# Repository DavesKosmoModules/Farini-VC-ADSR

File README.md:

# Farini-VC-ADSR

Voltage controlled AD / ADSR

- Envelope generator switchable between ADSR & AD
- Loopable
- End Of Cycle output
- Output can be inverted for ducking

- When in AD mode use the trigger input
- When in ADSR mode, use the gate input to start envelope, the trigger input will retigger the attach phase
- When in cycle mode use no inputs

 Contained are schematics & gerber files for pcb fabrication of both electrical and front panel. This is sutiable for entry level however a basic level of electronics, soldering, fault finding, and some basic tools are required.

 [Schematic](/Docs/Farini-Schematic.pdf)
 
 [BOM](Docs/Farini-BOM.pdf)

 If you wish to edit in ki-cad the following dependencies are required, however the component values will need tidying on the PCB as I use a forked version with no values.
 
  https://github.com/holmesrichards/Kosmo_panel
  
  https://github.com/holmesrichards/aoKicad

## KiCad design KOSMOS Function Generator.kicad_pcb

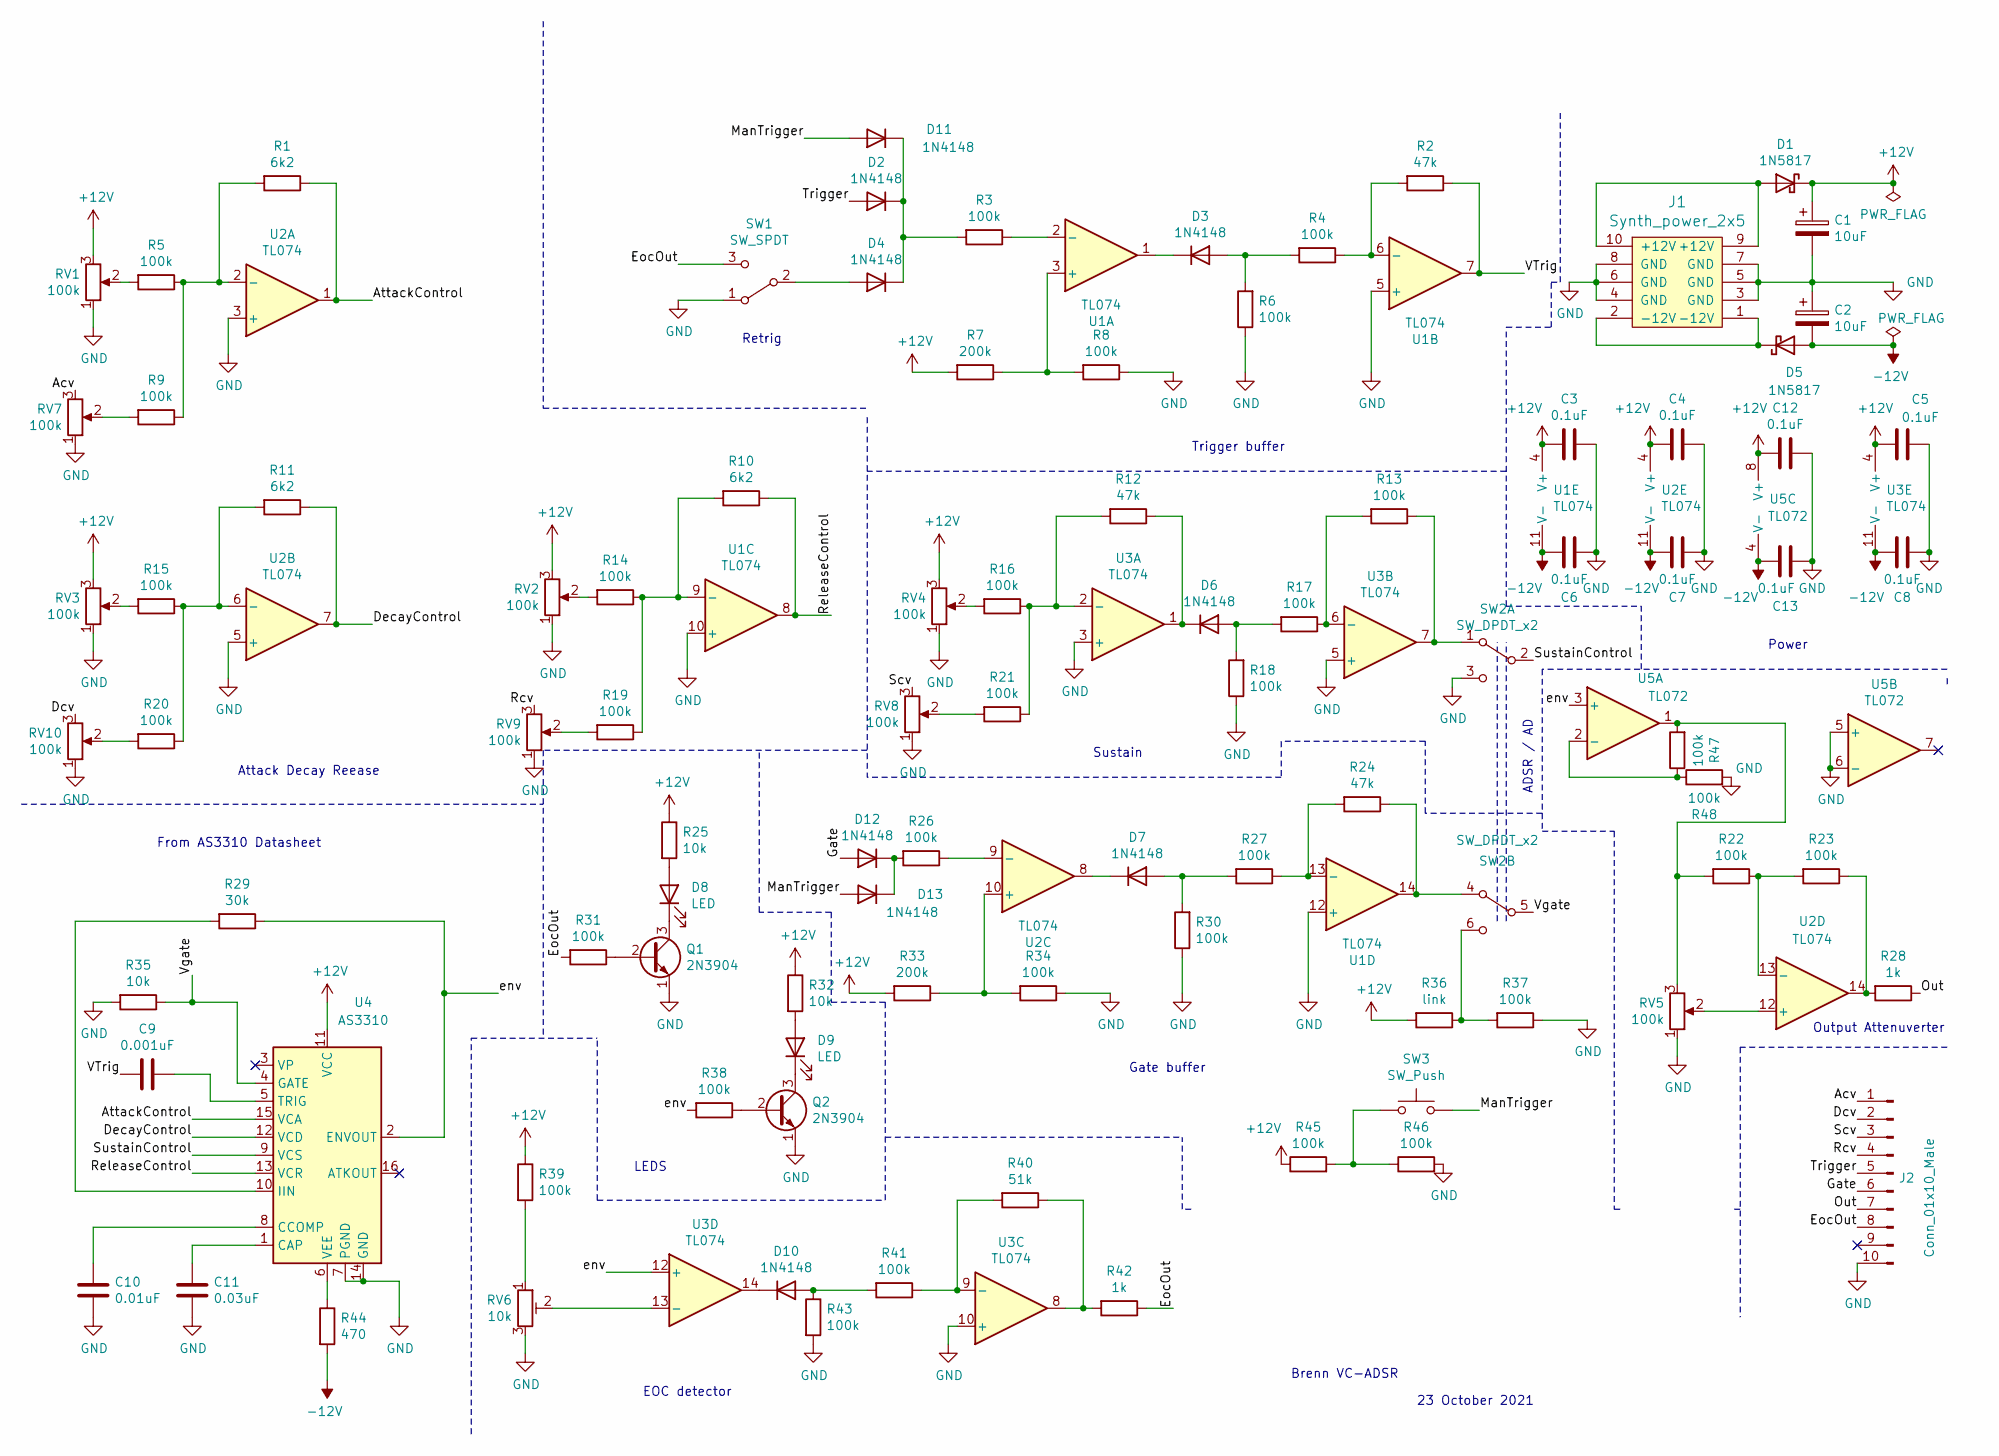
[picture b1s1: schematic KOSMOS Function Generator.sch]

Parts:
C1, C2: 10uF; CP_Radial_D6.3mm_P2.50mm
C3, C4, C5, C6, C7, C8, C12, C13: 0.1uF; C_Disc_D3.0mm_W1.6mm_P2.50mm
C9: 0.001uF; C_Disc_D3.0mm_W1.6mm_P2.50mm
C10: 0.01uF; C_Disc_D3.0mm_W1.6mm_P2.50mm
C11: 0.03uF; C_Disc_D3.0mm_W1.6mm_P2.50mm
D1, D5: 1N5817; D_DO-41_SOD81_P10.16mm_Horizontal
D2, D3, D4, D6, D7, D10, D11, D12, D13: 1N4148; D_DO-35_SOD27_P7.62mm_Horizontal
D8, D9: LED; LED_D5.0mm
J1: Synth_power_2x5; Power_Header
J2: Conn_01x10_Male; PinHeader_1x10_P2.54mm_Vertical
Q1, Q2: 2N3904; TO-92_Inline_Wide
R1, R10, R11: 6k2; R_Axial_DIN0207_L6.3mm_D2.5mm_P10.16mm_Horizontal
R2, R12, R24: 47k; R_Axial_DIN0207_L6.3mm_D2.5mm_P10.16mm_Horizontal
R3, R4, R5, R6, R8, R9, R13, R14, R15, R16, R17, R18, R19, R20, R21, R22, R23, R26, R27, R30, R31, R34, R37, R38, R39, R41, R43, R45, R46, R47, R48: 100k; R_Axial_DIN0207_L6.3mm_D2.5mm_P10.16mm_Horizontal
R7, R33: 200k; R_Axial_DIN0207_L6.3mm_D2.5mm_P10.16mm_Horizontal
R25, R32, R35: 10k; R_Axial_DIN0207_L6.3mm_D2.5mm_P10.16mm_Horizontal
R28, R42: 1k; R_Axial_DIN0207_L6.3mm_D2.5mm_P10.16mm_Horizontal
R29: 30k; R_Axial_DIN0207_L6.3mm_D2.5mm_P10.16mm_Horizontal
R36: link; R_Axial_DIN0207_L6.3mm_D2.5mm_P10.16mm_Horizontal
R40: 51k; R_Axial_DIN0207_L6.3mm_D2.5mm_P10.16mm_Horizontal
R44: 470; R_Axial_DIN0207_L6.3mm_D2.5mm_P10.16mm_Horizontal
RV1, RV2, RV3, RV4, RV5, RV7, RV8, RV9, RV10: 100k; Potentiometer_Alpha_RD901F-40-00D_Single_Vertical_CircularH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
RV6: 10k; Potentiometer_Alpha_RD901F-40-00D_Single_Vertical_CircularH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
SW1: SW_SPDT; SPDT-toggle-switch-1M-series
SW2: SW_DPDT_x2; DPDT-toggle-switch-1M-seriesx
SW3: SW_Push; Push_button_A-5050
U1, U2, U3: TL074; DIP-14_W7.62mm_Socket_LongPads
U4: AS3310; DIP-16_W7.62mm_Socket_LongPads
U5: TL072; DIP-8_W7.62mm_Socket_LongPads

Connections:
+12V: C1.1, C3.2, C4.2, C5.2, C12.2, D1.1 (K), R7.2, R25.1, R32.1, R33.2, R36.2, R39.1, R45.1, RV1.3, RV2.3, RV3.3, RV4.3, U1.4 (V+), U2.4 (V+), U3.4 (V+), U4.11 (VCC), U5.8 (V+)
-12V: C2.2, C6.2, C7.2, C8.2, C13.2, D5.2 (A), R44.2, U1.11 (V-), U2.11 (V-), U3.11 (V-), U5.4 (V-)
/Acv: J2.1, RV7.3
/AttackControl: R1.1, U2.1, U4.15 (VCA)
/Dcv: J2.2, RV10.3
/DecayControl: R11.1, U2.7, U4.12 (VCD)
/EocOut: J2.8, R31.2, R42.1, SW1.3 (C)
/Gate: D12.2 (A), J2.6
/ManTrigger: D11.2 (A), D13.2 (A), SW3.2
/Out: J2.7, R28.1
/Rcv: J2.4, RV9.3
/ReleaseControl: R10.1, U1.8, U4.13 (VCR)
/Scv: J2.3, RV8.3
/SustainControl: SW2.2 (B), U4.9 (VCS)
/Trigger: D2.2 (A), J2.5
/VTrig: C9.2, R2.1, U1.7
/Vgate: R35.1, SW2.5 (B), U4.4 (GATE)
/env: R29.1, R38.2, U3.12 (+), U4.2 (ENVOUT), U5.3 (+)
GND: C1.2, C2.1, C3.1, C4.1, C5.1, C6.1, C7.1, C8.1, C10.1, C11.1, C12.1, C13.1, J1.3 (GND), J1.4 (GND), J1.5 (GND), J1.6 (GND), J1.7 (GND), J1.8 (GND), J2.10, Q1.1 (E), Q2.1 (E), R6.1, R8.1, R18.1, R30.1, R34.1, R35.2, R37.1, R43.2, R46.2, R48.2, RV1.1, RV2.1, RV3.1, RV4.1, RV5.1, RV6.3, RV7.1, RV8.1, RV9.1, RV10.1, SW1.1 (A), SW2.3 (C), U1.5 (+), U1.10 (+), U1.12 (+), U2.3 (+), U2.5 (+), U3.3 (+), U3.5 (+), U3.10 (+), U4.7 (PGND), U4.14 (GND), U5.5 (+), U5.6 (-)
unnamed: C9.1, U4.5 (TRIG)
unnamed: C10.2, U4.8 (CCOMP)
unnamed: C11.2, U4.1 (CAP)
unnamed: D1.2 (A), J1.9 (+12V), J1.10 (+12V)
unnamed: D3.1 (K), U1.1
unnamed: D3.2 (A), R4.2, R6.2
unnamed: D4.2 (A), SW1.2 (B)
unnamed: D5.1 (K), J1.1 (-12V), J1.2 (-12V)
unnamed: D6.1 (K), R12.1, U3.1
unnamed: D6.2 (A), R17.2, R18.2
unnamed: D7.1 (K), U2.8
unnamed: D7.2 (A), R27.2, R30.2
unnamed: D8.1 (K), Q1.3 (C)
unnamed: D8.2 (A), R25.2
unnamed: D9.1 (K), Q2.3 (C)
unnamed: D9.2 (A), R32.2
unnamed: D10.1 (K), U3.14
unnamed: D10.2 (A), R41.2, R43.1
unnamed: D2.1 (K), D4.1 (K), D11.1 (K), R3.2
unnamed: D12.1 (K), D13.1 (K), R26.2
unnamed: Q1.2 (B), R31.1
unnamed: Q2.2 (B), R38.1
unnamed: R1.2, R5.1, R9.1, U2.2 (-)
unnamed: R2.2, R4.1, U1.6 (-)
unnamed: R3.1, U1.2 (-)
unnamed: R5.2, RV1.2
unnamed: R7.1, R8.2, U1.3 (+)
unnamed: R9.2, RV7.2
unnamed: R10.2, R14.1, R19.1, U1.9 (-)
unnamed: R11.2, R15.1, R20.1, U2.6 (-)
unnamed: R12.2, R16.1, R21.1, U3.2 (-)
unnamed: R13.1, SW2.1 (A), U3.7
unnamed: R13.2, R17.1, U3.6 (-)
unnamed: R14.2, RV2.2
unnamed: R15.2, RV3.2
unnamed: R16.2, RV4.2
unnamed: R19.2, RV9.2
unnamed: R20.2, RV10.2
unnamed: R21.2, RV8.2
unnamed: R22.1, R23.2, U2.13 (-)
unnamed: R22.2, R47.2, RV5.3, U5.1
unnamed: R23.1, R28.2, U2.14
unnamed: R24.1, SW2.4 (A), U1.14
unnamed: R24.2, R27.1, U1.13 (-)
unnamed: R26.1, U2.9 (-)
unnamed: R29.2, U4.10 (IIN)
unnamed: R33.1, R34.2, U2.10 (+)
unnamed: R36.1, R37.2, SW2.6 (C)
unnamed: R39.2, RV6.1
unnamed: R40.1, R42.2, U3.8
unnamed: R40.2, R41.1, U3.9 (-)
unnamed: R44.1, U4.6 (VEE)
unnamed: R45.2, R46.1, SW3.1
unnamed: R47.1, R48.1, U5.2 (-)
unnamed: RV5.2, U2.12 (+)
unnamed: RV6.2, U3.13 (-)

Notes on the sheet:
Output Attenuverter
Trigger buffer
Gate buffer
Retrig
ADSR / AD
From AS3310 Datasheet
LEDS
EOC detector
Sustain
Power
Attack Decay Reease
Brenn VC-ADSR
23 October 2021

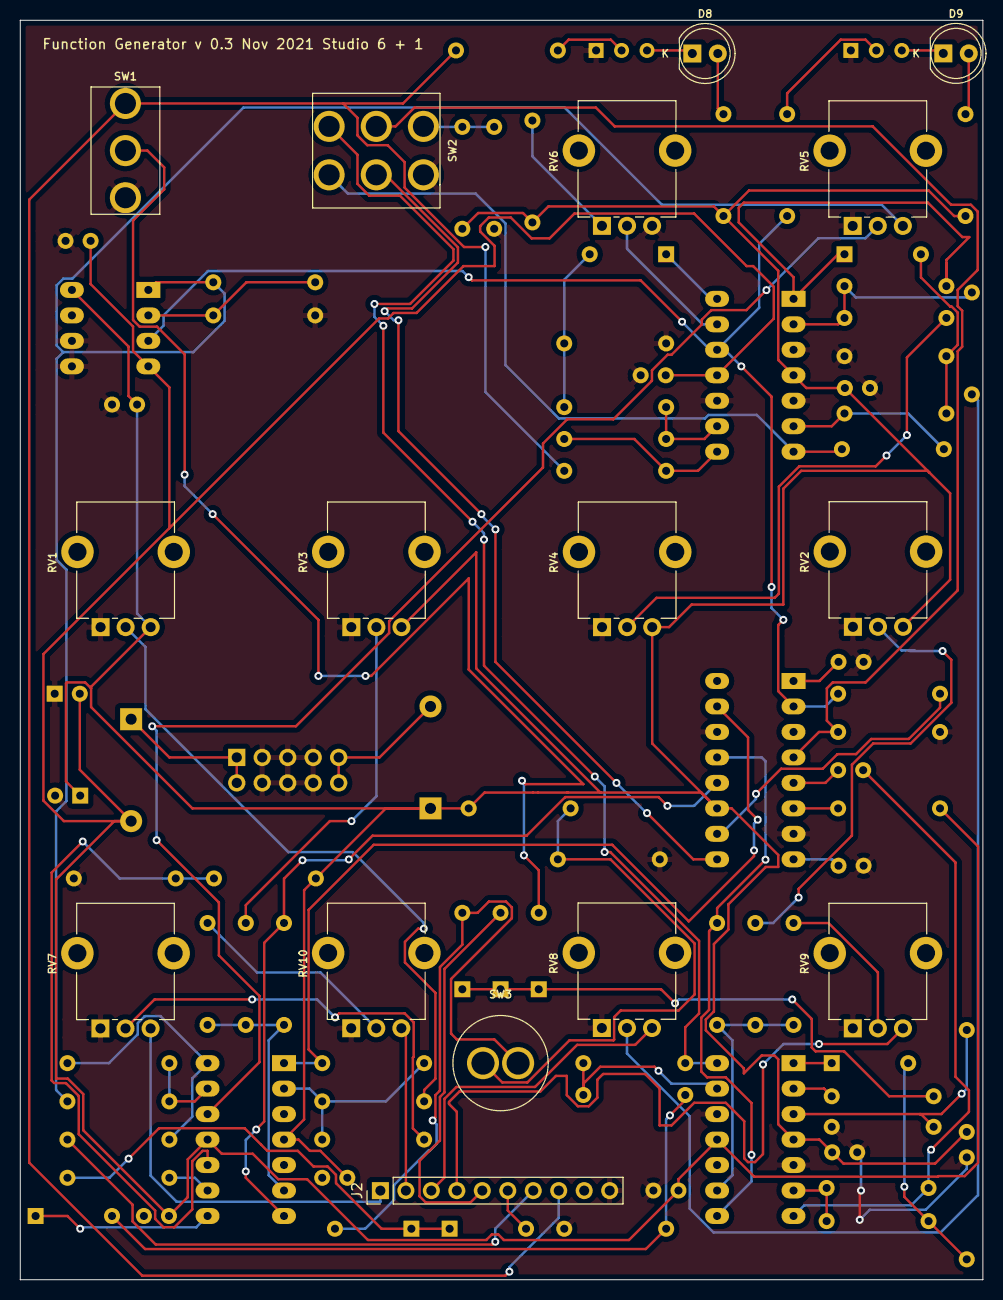
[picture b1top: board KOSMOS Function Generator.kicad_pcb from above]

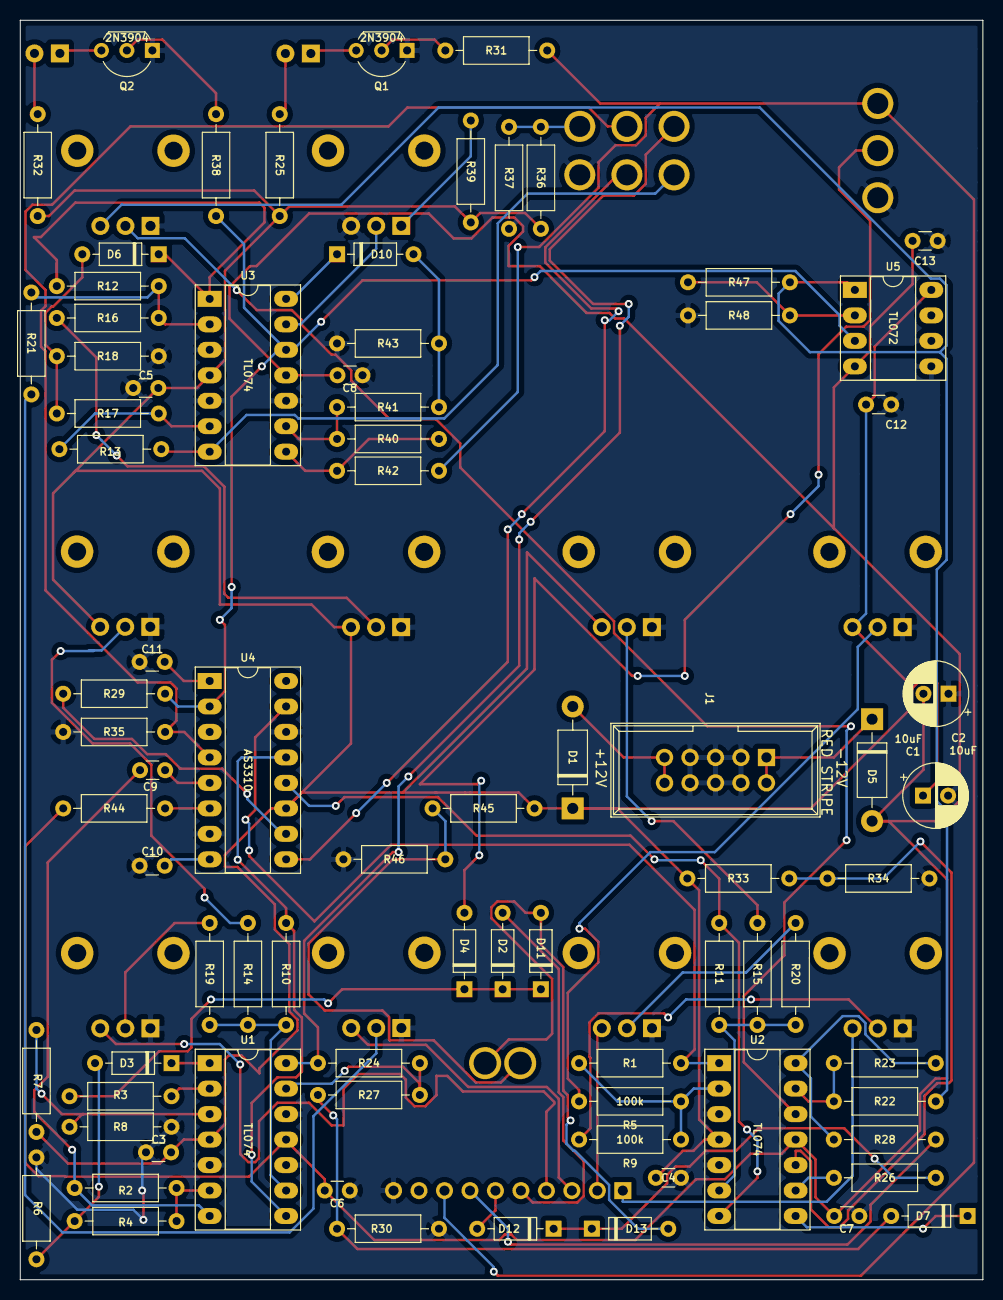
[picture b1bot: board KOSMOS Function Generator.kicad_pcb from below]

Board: 2 copper layers, 96.0 x 125.6 mm, 96 parts (80 on the bottom side), 75 nets.

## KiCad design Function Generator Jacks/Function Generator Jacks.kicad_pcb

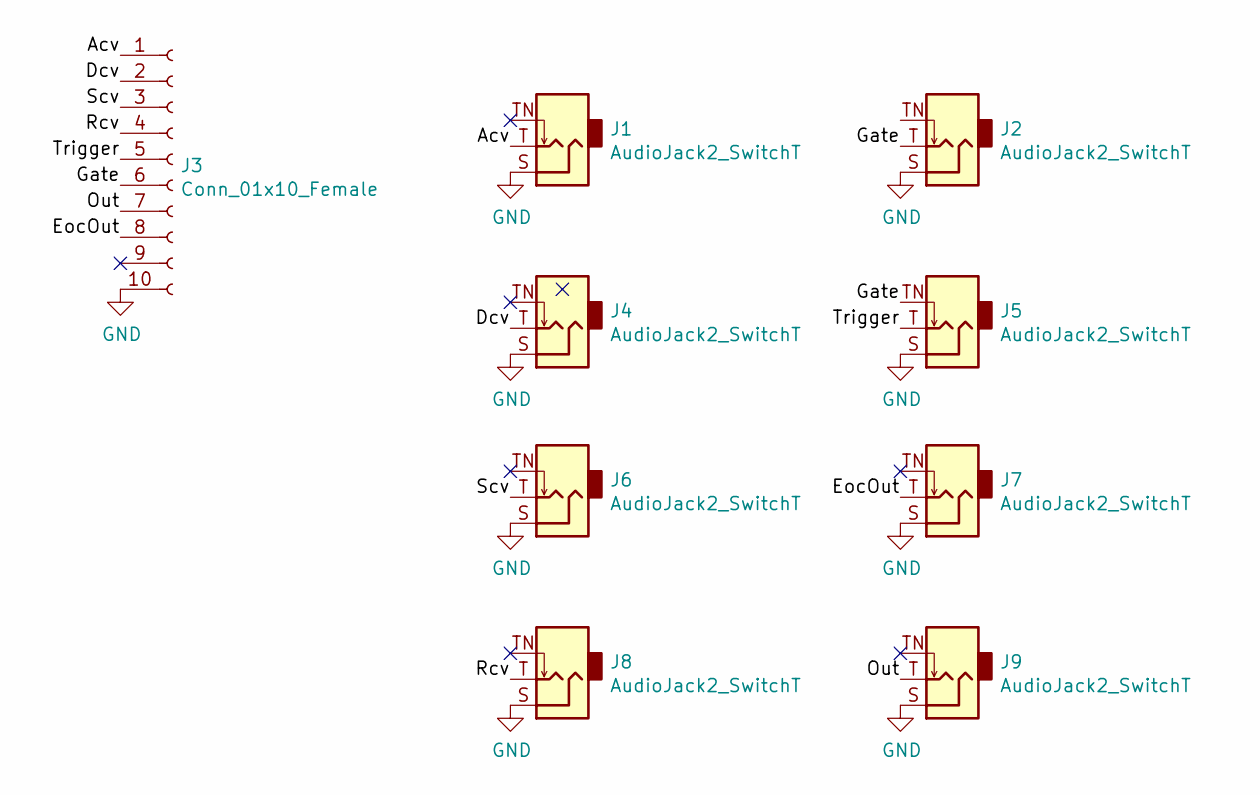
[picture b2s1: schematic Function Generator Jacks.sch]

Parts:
J1, J2, J4, J5, J6, J7, J8, J9: AudioJack2_SwitchT; Jack_6.35mm_PJ_629HAN
J3: Conn_01x10_Female; PinSocket_1x10_P2.54mm_Vertical

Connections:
/Acv: J1.T, J3.1
/Dcv: J3.2, J4.T
/EocOut: J3.8, J7.T
/Gate: J2.T, J3.6, J5.TN
/Out: J3.7, J9.T
/Rcv: J3.4, J8.T
/Scv: J3.3, J6.T
/Trigger: J3.5, J5.T
GND: J1.S, J2.S, J3.10, J4.S, J5.S, J6.S, J7.S, J8.S, J9.S

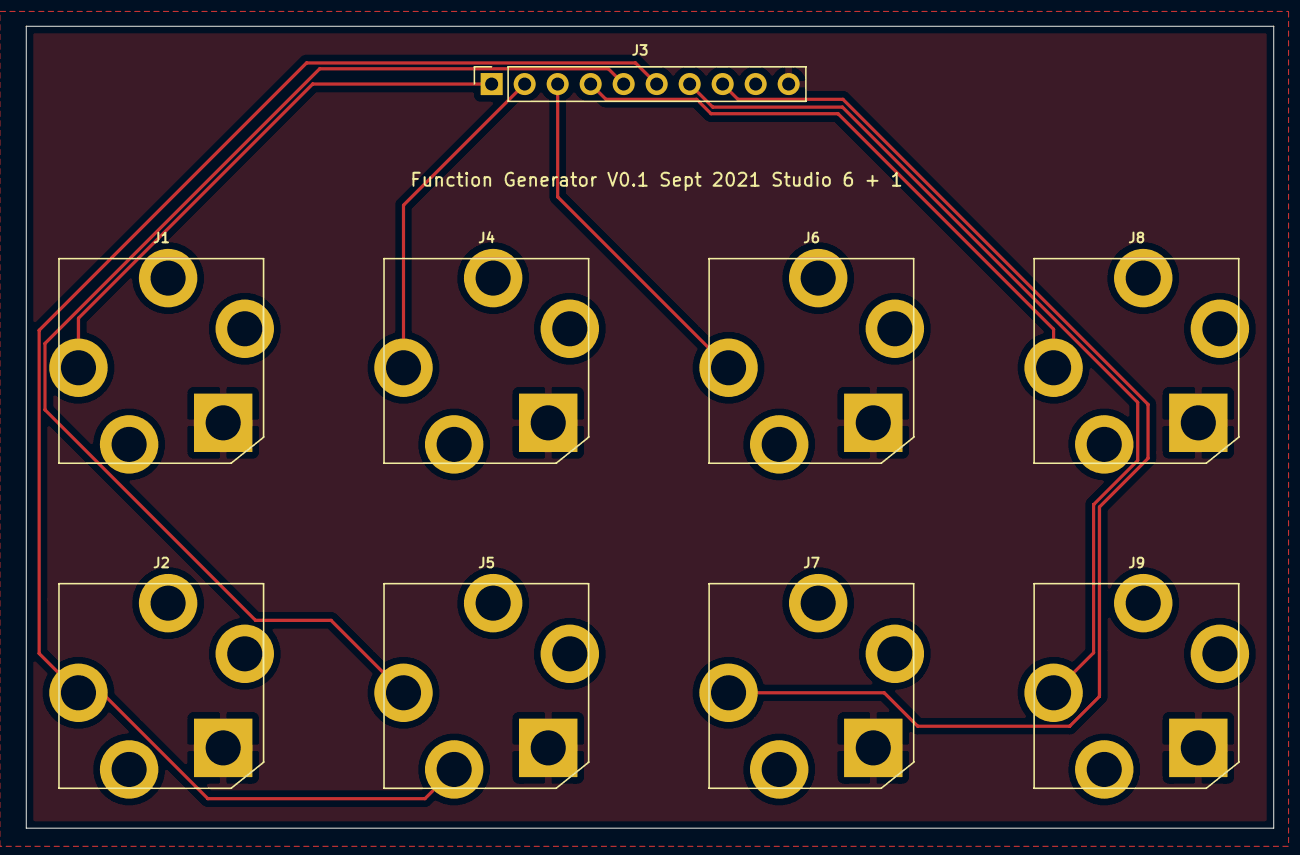
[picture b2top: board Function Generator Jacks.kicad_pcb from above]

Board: 2 copper layers, 96.0 x 61.7 mm, 9 parts (0 on the bottom side), 9 nets.

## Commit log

2021-10-23 Initial
2021-11-13 v03 pcb connect ground plane region
2021-11-14 pcb v03
